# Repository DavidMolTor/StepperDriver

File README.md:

# STEPPER DRIVER

A simple stepper driver module using a Seeed Studio Xiao development board and TMC2209 stepper driver IC.

## Introduction

This module is designed to be used as a stepper controller for a testbench platform.

The design is centered around the ESP32-C6 XIAO development board from Seeed Studio. It can be soldered as an SMD part in order to have access to the driver debug wire and JTAG connector on the board.

Compatibility with other drivers like the TMC2208 could be possible, the footprints for the different package needs to be checked before attempting to use it.

## Features

 - Wide input voltage range of 12-28V.

 - High current capability of up to 2.0A.

 - Wireless connectivity and LCD screen.

 - Afforable BOM with high quality parts.

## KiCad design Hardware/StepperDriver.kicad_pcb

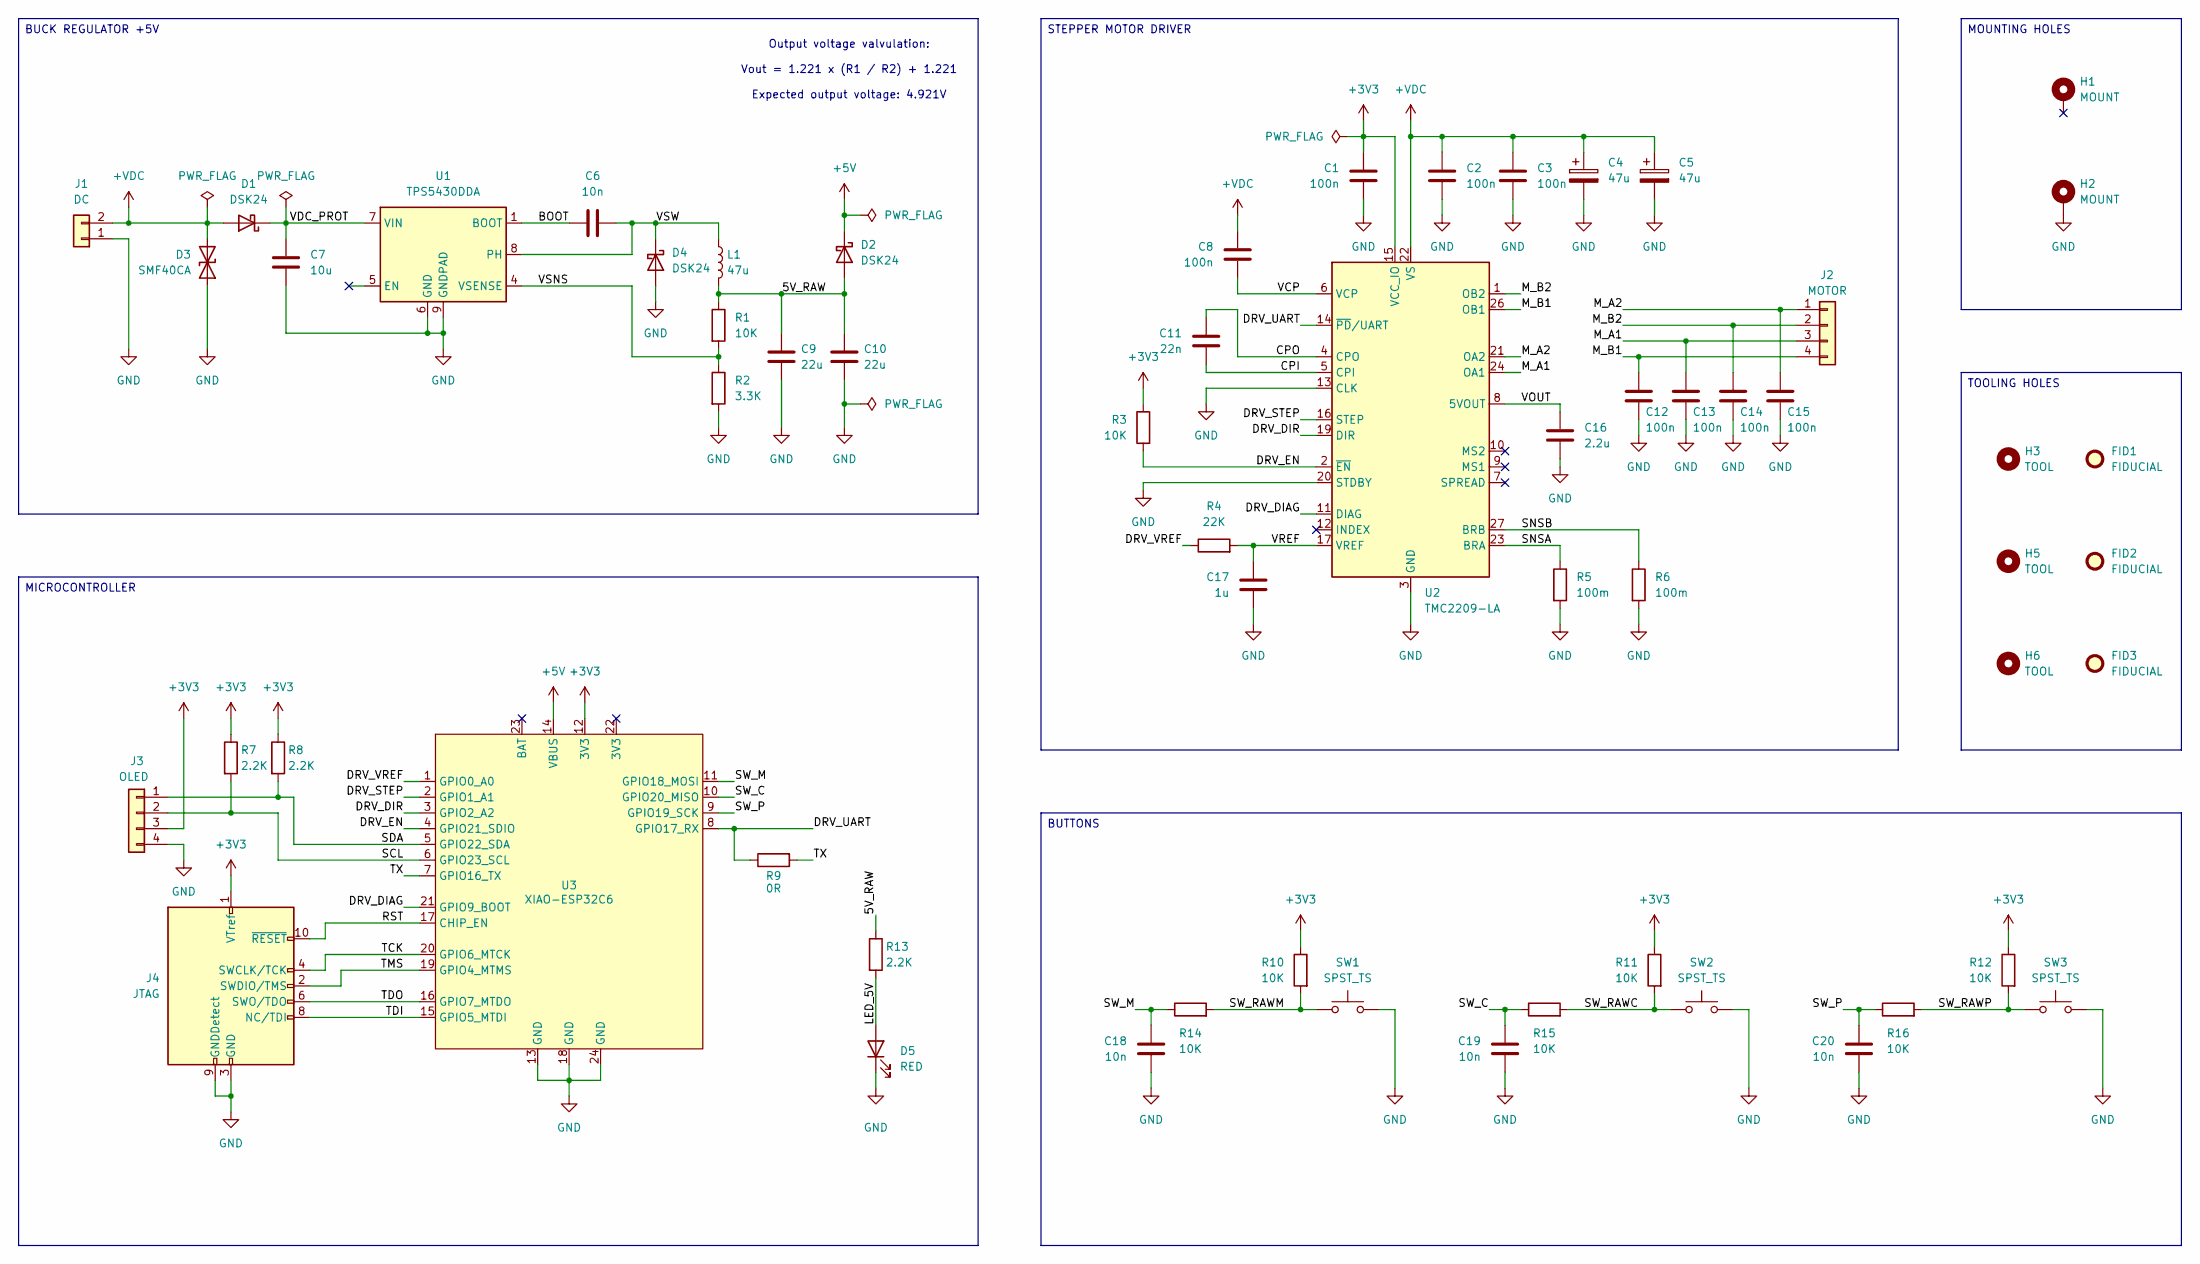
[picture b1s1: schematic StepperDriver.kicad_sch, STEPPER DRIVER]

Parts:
C1, C2, C3, C8, C12, C13, C14, C15: 100n; C_0603_1608Metric; Manufacturer Part CC0603KRX7R9BB104; JLCPCB Part C14663
C4, C5: 47u; CP_Elec_6.3x5.8; Manufacturer Part SVZ1VM470E06E00RAXXX; JLCPCB Part C721322
C6, C18, C19, C20: 10n; C_0603_1608Metric; Manufacturer Part 0603B103K500NT; JLCPCB Part C57112
C7: 10u; C_1206_3216Metric; Manufacturer Part CL31A106KBHNNNE; JLCPCB Part C13585
C9, C10: 22u; C_1206_3216Metric; Manufacturer Part CL31A226KAHNNNE; JLCPCB Part C12891
C11: 22n; C_0603_1608Metric; Manufacturer Part CL10B223KB8NNNC; JLCPCB Part C21122
C16: 2.2u; C_0603_1608Metric; Manufacturer Part CL10A225KO8NNNC; JLCPCB Part C23630
C17: 1u; C_0603_1608Metric; Manufacturer Part CL10A105KB8NNNC; JLCPCB Part C15849
D1, D2, D4: DSK24; D_SOD-123F; Manufacturer Part DSK24; JLCPCB Part C22466352
D3: SMF40CA; D_SOD-123F; Manufacturer Part SMF40CA; JLCPCB Part C42371749
D5: RED; LED_0603_1608Metric; Manufacturer Part KT-0603R; JLCPCB Part C2286
FID1, FID2, FID3: FIDUCIAL; Fiducial_0.75mm_Mask1.5mm
H1, H2: MOUNT; MountingHole_3.2mm_M3_Pad_Via
H3, H5, H6: TOOL; ToolingHole_1.152mm
J1: DC; JST_PH_S2B_1x02_COMBO; Manufacturer Part S2B-PH-K(LF)(SN); JLCPCB Part C265016
J2: MOTOR; JST_PH_S4B_1x04_COMBO; Manufacturer Part S4B-PH-K(LF)(SN); JLCPCB Part C265452
J3: OLED; HEADER_THROUGH_1x04_P2.54mm
J4: JTAG; PinHeader_2x05_P1.27mm_Vertical
L1: 47u; L_Changjiang_FNR5040S; Manufacturer Part FNR5040S470MT; JLCPCB Part C167974
R1, R3, R10, R11, R12, R14, R15, R16: 10K; R_0603_1608Metric; Manufacturer Part 0603WAF1002T5E; JLCPCB Part C25804
R2: 3.3K; R_0603_1608Metric; Manufacturer Part 0603WAF3301T5E; JLCPCB Part C22978
R4: 22K; R_0603_1608Metric; Manufacturer Part 0603WAF2202T5E; JLCPCB Part C31850
R5, R6: 100m; R_1206_3216Metric; Manufacturer Part 1206W4F100LT5E; JLCPCB Part C25334
R7, R8, R13: 2.2K; R_0603_1608Metric; Manufacturer Part 0603WAF2201T5E; JLCPCB Part C4190
R9: 0R; R_0603_1608Metric; Manufacturer Part 0603WAF0000T5E; JLCPCB Part C21189
SW1, SW2, SW3: SPST_TS; SW_SPST_TS-1088-xR020; Manufacturer Part TS-1088-AR02016; JLCPCB Part C720477
U1: TPS5430DDA; TI_SO-PowerPAD-8_ThermalVias; Manufacturer Part TPS5430DDAR; JLCPCB Part C9864
U2: TMC2209-LA; VQFN-28-1EP_5x5mm_P0.5mm_EP3.7x3.7mm_ThermalVias; Manufacturer Part TMC2209-LA-T; JLCPCB Part C2150710
U3: XIAO-ESP32C6; XIAO-ESP32C6-SMD

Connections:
+3V3: C1.1, J3.3, J4.1 (VTref), R3.1, R7.1, R8.1, R10.1, R11.1, R12.1, U2.15 (VCC_IO), U3.12 (3V3)
+5V: D2.1 (K), U3.14 (VBUS)
+VDC: C2.1, C3.1, C4.1, C5.1, C8.1, D1.2 (A), D3.2 (A2), J1.2, U2.22 (VS), U2.28 (VS)
/5V_RAW: C9.1, C10.1, D2.2 (A), L1.2, R1.1, R13.1
/BOOT: C6.1, U1.1 (BOOT)
/CPI: C11.2, U2.5 (CPI)
/CPO: C11.1, U2.4 (CPO)
/DRV_DIAG: U2.11 (DIAG), U3.21 (GPIO9_BOOT)
/DRV_DIR: U2.19 (DIR), U3.3 (GPIO2_A2)
/DRV_EN: R3.2, U2.2 (~EN), U3.4 (GPIO21_SDIO)
/DRV_STEP: U2.16 (STEP), U3.2 (GPIO1_A1)
/DRV_UART: R9.1, U2.14 (~PD/UART), U3.8 (GPIO17_RX)
/DRV_VREF: R4.1, U3.1 (GPIO0_A0)
/LED_5V: D5.2 (A), R13.2
/M_A1: C13.1, J2.3, U2.24 (OA1)
/M_A2: C15.1, J2.1, U2.21 (OA2)
/M_B1: C12.1, J2.4, U2.26 (OB1)
/M_B2: C14.1, J2.2, U2.1 (OB2)
/RST: J4.10 (~RESET), U3.17 (CHIP_EN)
/SCL: J3.2, R7.2, U3.6 (GPIO23_SCL)
/SDA: J3.1, R8.2, U3.5 (GPIO22_SDA)
/SNSA: R5.1, U2.23 (BRA)
/SNSB: R6.1, U2.27 (BRB)
/SW_C: C19.1, R15.1, U3.10 (GPIO20_MISO)
/SW_M: C18.1, R14.1, U3.11 (GPIO18_MOSI)
/SW_P: C20.1, R16.1, U3.9 (GPIO19_SCK)
/SW_RAWC: R11.2, R15.2, SW2.1
/SW_RAWM: R10.2, R14.2, SW1.1
/SW_RAWP: R12.2, R16.2, SW3.1
/TCK: J4.4 (SWCLK/TCK), U3.20 (GPIO6_MTCK)
/TDI: J4.8 (NC/TDI), U3.15 (GPIO5_MTDI)
/TDO: J4.6 (SWO/TDO), U3.16 (GPIO7_MTDO)
/TMS: J4.2 (SWDIO/TMS), U3.19 (GPIO4_MTMS)
/TX: R9.2, U3.7 (GPIO16_TX)
/VCP: C8.2, U2.6 (VCP)
/VDC_PROT: C7.1, D1.1 (K), U1.7 (VIN)
/VOUT: C16.1, U2.8 (5VOUT)
/VREF: C17.1, R4.2, U2.17 (VREF)
/VSNS: R1.2, R2.1, U1.4 (VSENSE)
/VSW: C6.2, D4.1 (K), L1.1, U1.8 (PH)
GND: C1.2, C2.2, C3.2, C4.2, C5.2, C7.2, C9.2, C10.2, C12.2, C13.2, C14.2, C15.2, C16.2, C17.2, C18.2, C19.2, C20.2, D3.1 (A1), D4.2 (A), D5.1 (K), H2.1 (1_1), J1.1, J3.4, J4.3 (GND), J4.5 (GND), J4.9 (GNDDetect), R2.2, R5.2, R6.2, SW1.2, SW2.2, SW3.2, U1.6 (GND), U1.9 (GNDPAD), U2.3 (GND), U2.13 (CLK), U2.18 (GND), U2.20 (STDBY), U2.29 (GND), U3.13 (GND), U3.18 (GND), U3.24 (GND)

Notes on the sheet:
Output voltage valvulation: Vout = 1.221 x (R1 / R2) + 1.221 Expected output voltage: 4.921V
TOOLING HOLES
MICROCONTROLLER
MOUNTING HOLES
BUTTONS
BUCK REGULATOR +5V
STEPPER MOTOR DRIVER

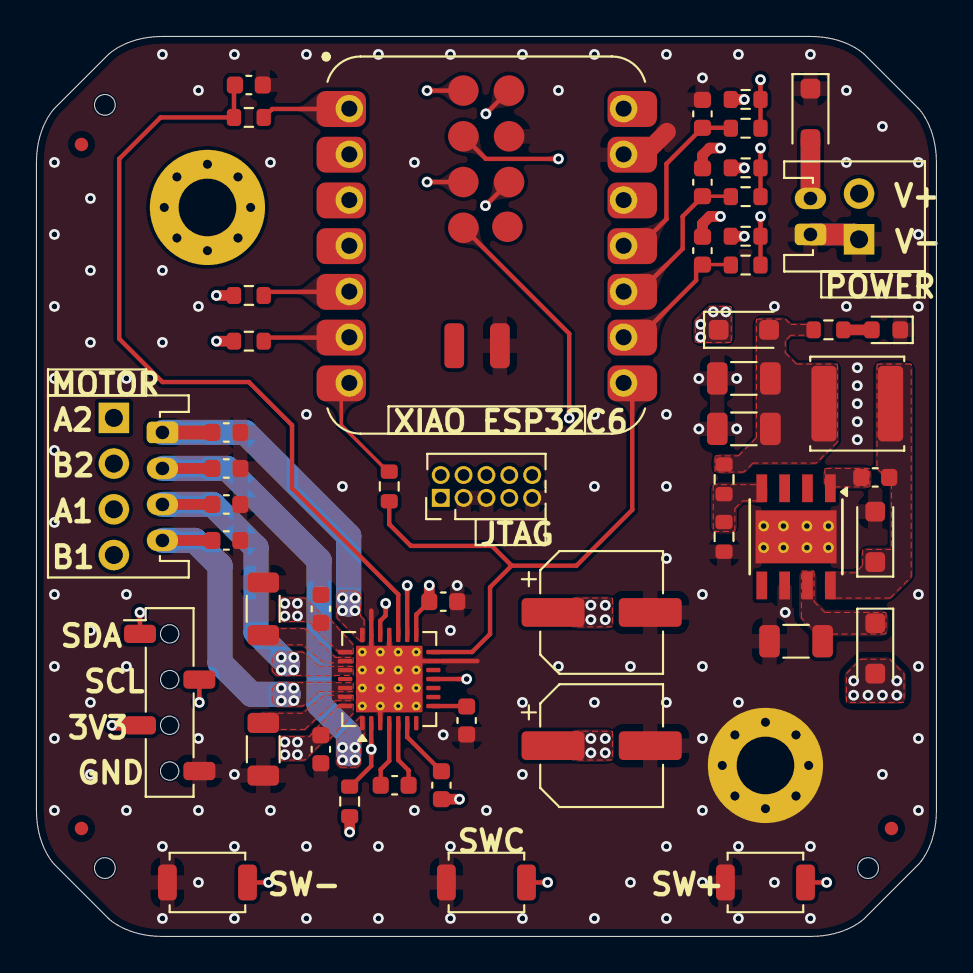
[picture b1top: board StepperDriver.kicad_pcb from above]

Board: 6 copper layers, 50.0 x 50.0 mm, 60 parts (0 on the bottom side), 41 nets.

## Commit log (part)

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2026-05-19 Project files
    Added the KiCAD project files.
    Added a readme file.
    Added a license file.
    Added a gitignore file.
2026-05-19 Readme
    Updated the readme file.
2026-05-20 Initial schematic
    Completed the first iteration for the schematic.
    Included a default 42x42mm PCB area.
2026-05-21 Initial layout
    Completed the first iteration for the layout.
    Increased the PCB area to 50x50mm.
    Minor changes in the schematic.
2026-05-21 Initial ESP32C6 layout
    Moved to a XIAO ESP32C6 development board.
    Completed the first iteration for the layout.
2026-05-21 Build output files
    Generated the output files for the first iteration of the ESP32-C6 board.
    Added some board images and 3D model.
    Added the BOM and POS files for assembly.
2026-05-21 Assembly revision
    Minor changes to the board and schematic.
    Updated the output files.
2026-05-21 File names
    Updated some of the names for the output files.
2026-05-21 Build output files
    Rounded the corners of the board.
    Updated the output files and added a spacer model.
2026-05-22 Driver update
    Moved to the better TMC2209 stepper motor driver.
    Added a status LED for the voltage regulator.
    Updated the output files.
2026-05-22 Output files
    Minor changes on the PCB.
    Updated the bulk capacitors for the board to have a lower voltage rating.
2026-05-23 Output files
    Minor changes to the board and schematic.
    Updated the output files.
2026-05-25 Assembly review
    Performed a full review of the schematic and layout.
    Minor changes to the schematic and layout.
    Updated output files.
2026-06-05 Initial control software
    Added a basic Arduino program to control the speed of the motor via UART named BasicStepper.
    Added the initial driver for the board named SimpleStepper.
2026-06-05 Basic driver upgrade
    Upgraded the basic Arduino code so that the speed and microstepping can be controlled using the onboard buttons.
2026-06-05 Simple Arduino drivers
    Updated the basic Arduino motor driver code.
    Added a new driver using the step and direction pin with the Arduino libraries.
2026-06-05 Initial ESP-IDF project
    Added an intial ESP-IDF project for VS Code.
    Included all GPIO configurations under the project GUI manager.
2026-06-07 OTA application example
    Added OTA update functionality to the main project.
    Added an mDNS host name for easy HTTP resolution.
    Added a working serial console interface.
2026-06-10 Stepper driver software
    Unified the basic and simple driver Arduino code.
    Updated the ESP-IDF prior to adding the TMC2209 driver class.
2026-06-10 TMC2209 driver class
    Added the driver class for the TMC2209.
    Revieww the UART communication between the MCU and the stepper driver.
2026-06-10 TCM2209 driver UART
    Updated the UART comms for the TMC2209.
    Success on testing the TCM2209 initial setup via UART.
